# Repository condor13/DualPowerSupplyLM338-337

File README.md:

Linear Power Supply for Synthesizers (+12V, -12V, +5V)
A high-quality, low-noise linear power supply designed specifically for analog synthesizers.

Features
Triple Rail Output: +12V, -12V, and +5V rails.
High Current Capability: Equipped with LM338 (5A) for positive rails and LM337 (1.5A) for the negative rail.
Adjustable Precision: Multi-turn trimmers allow for exact voltage calibration (e.g., exactly 5.00V).
Robust Protection: Includes 1N4007 back-EMF protection diodes on all stages.

Hardware Specifications
Input: Transformer with 18V-0-18V and 10V secondaries.
Regulation: LM338T (Pos), LM337T (Neg).
Thermal: Designed for external heatsink mounting with electrical isolation.

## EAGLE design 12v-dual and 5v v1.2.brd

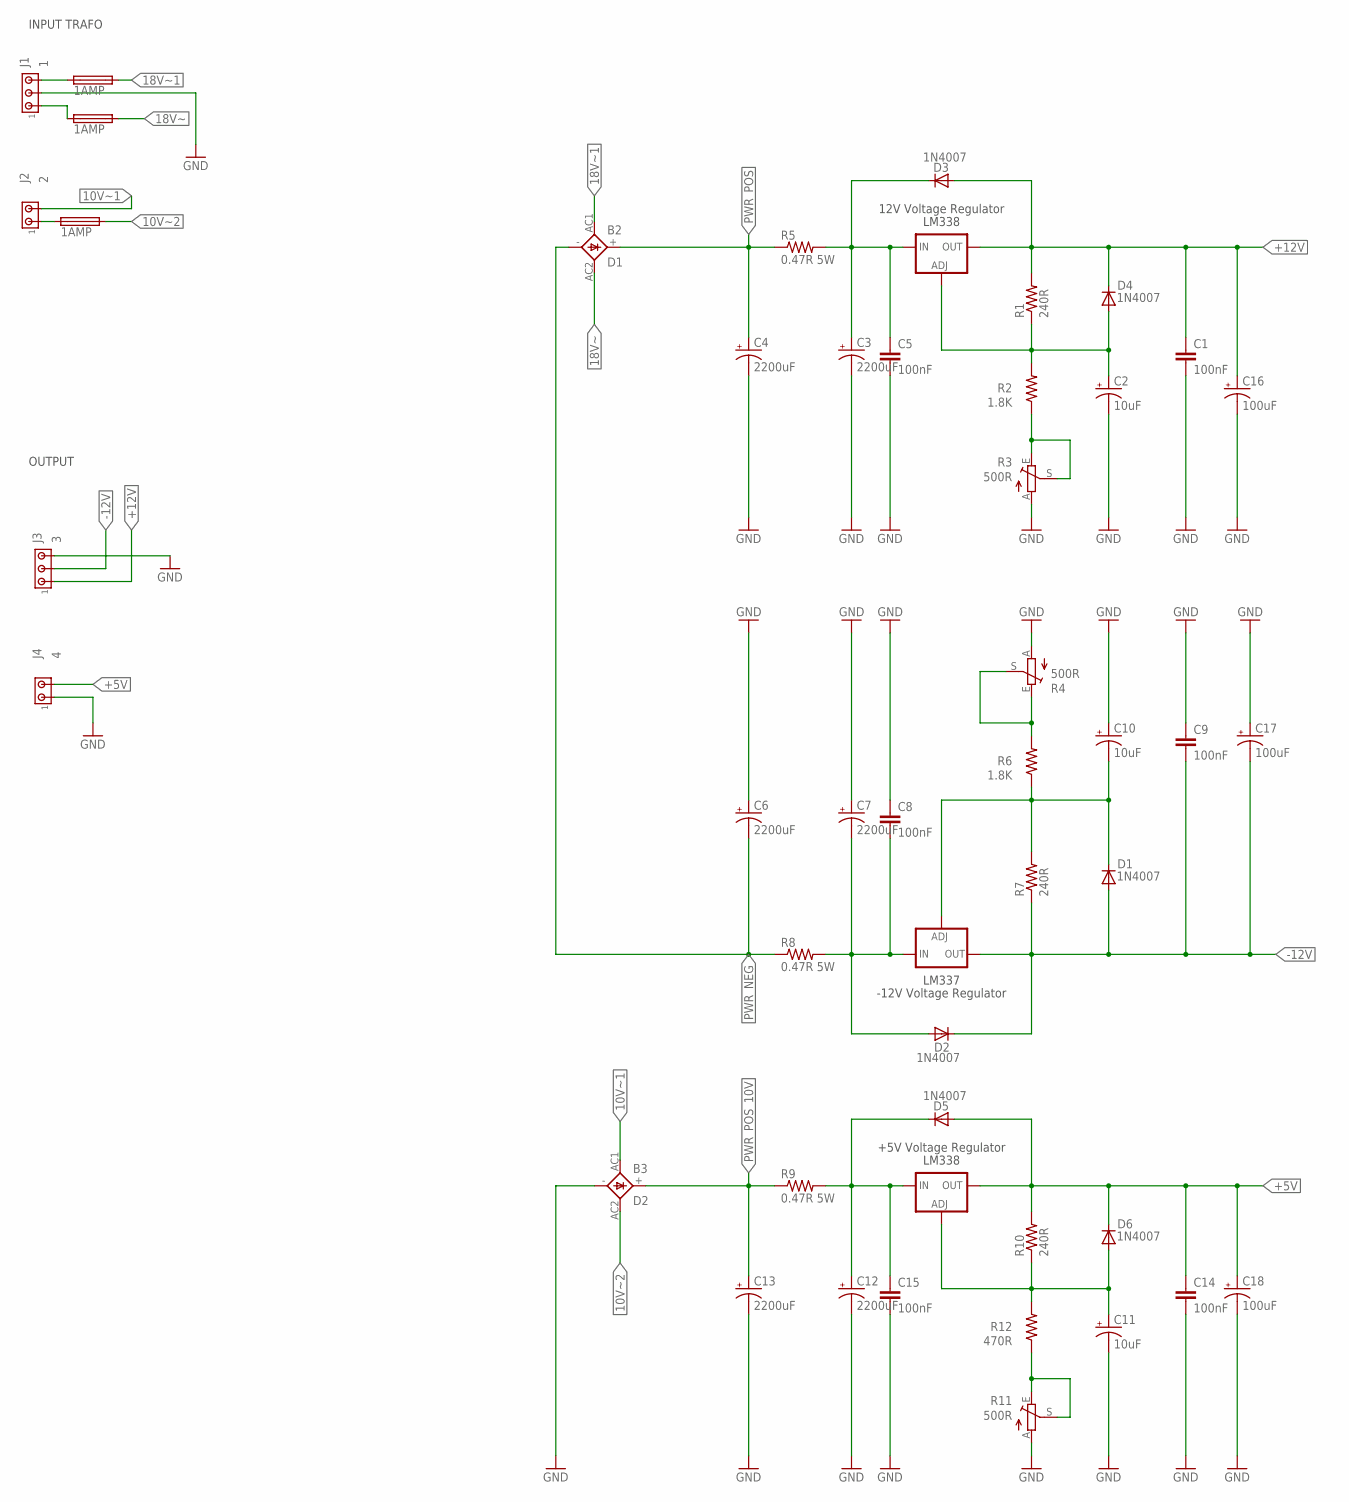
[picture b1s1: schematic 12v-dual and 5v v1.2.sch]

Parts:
B2: D1; FB15
B3: D2; FB15
C1, C5, C8, C9, C14, C15: 100nF; C050-025X075
C2, C10, C11: 10uF; E2-5
C3, C4, C6, C7, C12, C13: 2200uF; E5-13
C16, C17, C18: 100uF; E2-5
D1, D2, D3, D4, D5, D6: 1N4007; DO41-10
F1, F2, F3: 1AMP; SH25
IC1: LM337; 337TS
IC2: LM338; 317TS; PARTNUMBER LM317M
IC3: LM317MB; 317TS; PARTNUMBER LM317M
J1: 1; 1X3MTA
J2: 2; 1X2MTA
J3: 3; 1X3MTA
J4: 4; 1X2MTA
R1, R7, R10: 240R; 0204/7
R2, R6: 1.8K; 0204/7
R3, R4, R11: 500R; RJ9W
R5, R8, R9: 0.47R 5W; 0617/17
R12: 470R; 0204/7

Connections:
10V~1: B3.AC1, J2.2
10V~2: B3.AC2, F3.2
18V~: B2.AC2, F2.2
18V~1: B2.AC1, F1.2
18V~2: F2.1, J1.1
+5V: C14.1, C18.+, D5.A, D6.C, IC3.2 (OUT), J4.2, R10.2
+12V: C1.1, C16.+, D3.A, D4.C, IC2.2 (OUT), J3.1, R1.2
-12V: C9.2, C17.-, D1.A, D2.C, IC1.3 (OUT), J3.2, R7.1
ADJ-NEG: C10.-, D1.C, IC1.1 (ADJ), R6.1, R7.2
ADJ-POS: C2.+, D4.A, IC2.1 (ADJ), R1.1, R2.2
ADJ-POS1: C11.+, D6.A, IC3.1 (ADJ), R10.1, R12.2
GND: B3.-, C1.2, C2.-, C3.-, C4.-, C5.2, C6.+, C7.+, C8.1, C9.1, C10.+, C11.-, C12.-, C13.-, C14.2, C15.2, C16.-, C17.+, C18.-, J1.2, J3.3, J4.1, R3.A, R4.A, R11.A
unnamed: R2.1, R3.E, R3.S
unnamed: R11.E, R11.S, R12.1
unnamed: F1.1, J1.3
unnamed: F3.1, J2.1
unnamed: R4.E, R4.S, R6.2
NEG-IN: C7.-, C8.2, D2.A, IC1.2 (IN), R8.2
PWR_NEG: B2.-, C6.-, R8.1
PWR_POS: B2.+, C4.+, R5.1
PWR_POS_10V: B3.+, C13.+, R9.1
VIN: C3.+, C5.1, D3.C, IC2.3 (IN), R5.2
VIN1: C12.+, C15.1, D5.C, IC3.3 (IN), R9.2

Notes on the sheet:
+5V Voltage Regulator
-12V Voltage Regulator
12V Voltage Regulator
LM337
LM338
INPUT TRAFO
OUTPUT

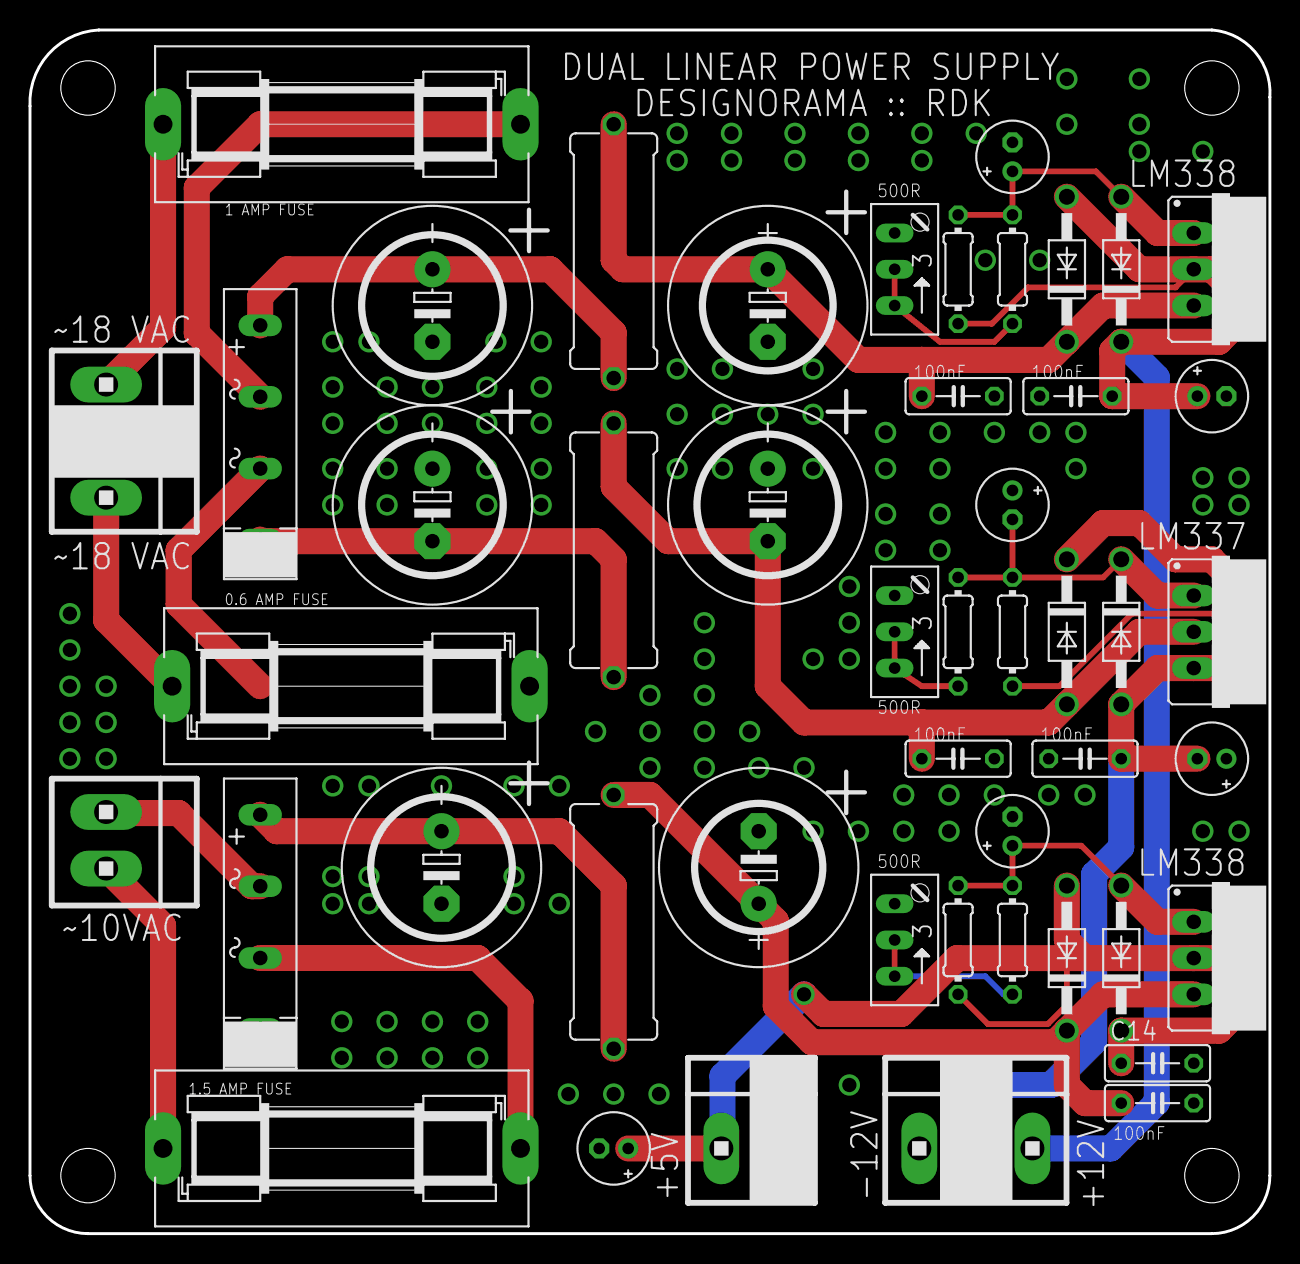
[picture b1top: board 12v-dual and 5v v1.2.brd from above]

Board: 2 copper layers, 86.9 x 84.3 mm, 48 parts (0 on the bottom side), 23 nets.
